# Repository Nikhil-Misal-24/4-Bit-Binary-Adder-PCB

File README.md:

# 4-Bit Binary Adder Using 74HC Logic ICs

A through-hole, discrete-logic **4-bit ripple-carry adder** built from 74HC86 (XOR), 74HC08 (AND) and 74HC32 (OR) ICs, with push-button inputs, LED indicators and a PCB designed in **KiCad**.

> **Project status:** The schematic and final PCB layout are complete in KiCad. This README makes **no claim** that the board has been fabricated, assembled or tested. All results below are *theoretical expected values*. Items marked **⚠ Confirm** should be checked before fabrication.

## At a Glance

| Parameter | Specification |
|---|---|
| Function | Adds two 4-bit unsigned binary numbers |
| Inputs | 8 push switches: A0–A3 and B0–B3 |
| Output | 5-bit result `Cout S3 S2 S1 S0` (range 0 to 30) on 5 LEDs |
| Architecture | Half adder (bit 0) + three full adders (bits 1–3), ripple-carry |
| Logic ICs | 2× 74HC86 (XOR), 2× 74HC08 (AND), 1× 74HC32 (OR) |
| Supply | Regulated 5 V DC via barrel jack, fuse and power switch |
| PCB | KiCad, through-hole, appears to be 2-layer |
| Hardware status | Fabrication and testing **not yet verified** |

---

## Table of Contents

1. [Introduction](#1-introduction)
2. [Project Overview](#2-project-overview)
3. [Key Features](#3-key-features)
4. [Objectives and Learning Outcomes](#4-objectives-and-learning-outcomes)
5. [Working Principle of a 4-Bit Binary Adder](#5-working-principle-of-a-4-bit-binary-adder)
6. [Boolean Expressions and Logic Equations](#6-boolean-expressions-and-logic-equations)
7. [Circuit Architecture and Block Diagram](#7-circuit-architecture-and-block-diagram)
8. [Hardware Components](#8-hardware-components)
9. [Input and Output Explanation](#9-input-and-output-explanation)
10. [Circuit Operation: Worked Example](#10-circuit-operation-worked-example)
11. [Expected Output and Verification Test Cases](#11-expected-output-and-verification-test-cases)
12. [Power Supply Requirements and Safety Precautions](#12-power-supply-requirements-and-safety-precautions)
13. [PCB Design Details and KiCad Files](#13-pcb-design-details-and-kicad-files)
14. [Repository Folder Structure](#14-repository-folder-structure)
15. [How to Open the Project in KiCad](#15-how-to-open-the-project-in-kicad)
16. [Testing and Troubleshooting](#16-testing-and-troubleshooting)
17. [Applications](#17-applications)
18. [Limitations and Possible Future Improvements](#18-limitations-and-possible-future-improvements)
19. [Skills Demonstrated](#19-skills-demonstrated)
20. [Author and Acknowledgements](#20-author-and-acknowledgements)

---

## 1. Introduction

Adders are the foundation of every arithmetic logic unit (ALU). This project implements a 4-bit binary adder **using only basic logic gates** (XOR, AND, OR) instead of a ready-made adder IC such as the 74HC283. Building it gate by gate makes the carry mechanism visible and testable on real hardware.

## 2. Project Overview

The circuit adds two 4-bit unsigned numbers, **A (A3 A2 A1 A0)** and **B (B3 B2 B1 B0)**, entered with eight push switches. The result is a **5-bit value** shown on five LEDs:

```
Result = Cout S3 S2 S1 S0
```

- **S0–S3** are the four sum bits (S0 = LSB).
- **Cout** is the final carry out of bit 3 and acts as the fifth (most significant) result bit.

The maximum result is 1111 + 1111 = 11110 (15 + 15 = 30), which needs 5 bits.

The board also has eight **input-indicator LEDs** (D1–D8) that mirror the state of each input switch, plus five **output LEDs** (D9–D13).

## 3. Key Features

- Pure gate-level design: 2× 74HC86, 2× 74HC08, 1× 74HC32.
- Two 4-bit inputs, 5-bit output (sum + carry).
- Input-state LEDs for each switch, so the entered operands can be read directly from the board.
- 10 kΩ pull-down resistors for defined logic-low inputs.
- Five 100 nF decoupling capacitors (C1–C5), one beside each IC.
- 220 Ω series resistors on every LED.
- Power entry through a barrel jack with a fuse and an on/off switch.
- Through-hole, breadboard-style parts, easy to hand-solder and probe.
- Silkscreen reference table for 4-bit values 0–15 on the board.
- Complete KiCad schematic and 2-layer PCB layout.

## 4. Objectives and Learning Outcomes

**Objectives**

- Design a multi-bit adder from XOR, AND and OR gates.
- Translate a schematic into a PCB layout using KiCad.
- Add clear user interface elements (switches, LEDs, silkscreen) to a logic board.

**Learning outcomes**

- Derive half-adder and full-adder equations and cascade them.
- Understand ripple-carry propagation and its speed limitation.
- Understand CMOS logic practice: pull-downs, unused-input handling, decoupling and LED current limiting.
- Practice schematic capture, footprint assignment, routing, DRC and design documentation.

## 5. Working Principle of a 4-Bit Binary Adder

Binary addition works like decimal addition, column by column, from the least significant bit (LSB) to the most significant bit (MSB). In each column we add two input bits plus the carry coming from the previous column.

| Building block | Inputs | Outputs | Used for |
|---|---|---|---|
| **Half adder** | A, B | Sum, Carry | Bit 0 (no carry-in) |
| **Full adder** | A, B, Cin | Sum, Cout | Bits 1, 2, 3 |

**Ripple-carry principle.** The carry-out of each stage feeds the carry-in of the next stage:

```
C0 = 0 → [Bit 0] → C1 → [Bit 1] → C2 → [Bit 2] → C3 → [Bit 3] → C4 = Cout
```

Bit *i* cannot produce a valid sum until the carry from bit *i−1* has settled. The carry therefore "ripples" from the LSB to the MSB. The worst case (e.g. `1111 + 0001`) makes the carry travel through all four stages, which is why the delay grows with word length.

## 6. Boolean Expressions and Logic Equations

For each bit *i*, define the **propagate** signal $P_i$ and **generate** signal $G_i$:

$$P_i = A_i \oplus B_i \qquad G_i = A_i \cdot B_i$$

**Bit 0 (half adder, $C_0 = 0$):**

$$S_0 = A_0 \oplus B_0 \qquad C_1 = A_0 \cdot B_0$$

**Bits 1 to 3 (full adder):**

$$S_i = A_i \oplus B_i \oplus C_i = P_i \oplus C_i$$

$$C_{i+1} = A_i B_i + (A_i \oplus B_i)\,C_i = G_i + P_i C_i$$

**Final carry (fifth output bit):**

$$C_{out} = C_4$$

**Gate budget (derived from the equations):**

| Gate type | Needed | Available (ICs fitted) | Spare |
|---|---|---|---|
| XOR (74HC86) | 7 | 8 (2 ICs) | 1 |
| AND (74HC08) | 7 | 8 (2 ICs) | 1 |
| OR (74HC32) | 3 | 4 (1 IC) | 1 |

Gate truth tables:

| A | B | XOR (A⊕B) | AND (A·B) | OR (A+B) |
|:-:|:-:|:-:|:-:|:-:|
| 0 | 0 | 0 | 0 | 0 |
| 0 | 1 | 1 | 0 | 1 |
| 1 | 0 | 1 | 0 | 1 |
| 1 | 1 | 0 | 1 | 1 |

## 7. Circuit Architecture and Block Diagram

### 7.1 System-level block diagram

The design is split into four functional blocks: **power**, **input stage**, **logic core** and **output stage**.

```mermaid
flowchart LR
    PWR["POWER<br/>J1 - F1 - SW1<br/>regulated +5 V"]

    subgraph INP["INPUT STAGE"]
        direction TB
        SWA["SW2, SW4, SW6, SW8<br/>Operand A (A0-A3)"]
        SWB["SW3, SW5, SW7, SW9<br/>Operand B (B0-B3)"]
        IND["10 kOhm pull-downs<br/>Indicator LEDs D1-D8"]
    end

    subgraph CORE["LOGIC CORE - 74HC ICs"]
        direction TB
        XORS["XOR: U1, U2<br/>74HC86"]
        ANDS["AND: U3, U4<br/>74HC08"]
        ORS["OR: U5<br/>74HC32"]
    end

    subgraph OUT["OUTPUT STAGE"]
        direction TB
        RES["220 Ohm resistors<br/>R17-R21"]
        LEDS["LEDs D13-D9<br/>Cout S3 S2 S1 S0"]
    end

    PWR -- "INPUT_VCC" --> INP
    PWR -- "VCC + C1-C5" --> CORE
    INP -- "A0-A3, B0-B3" --> CORE
    CORE -- "S0-S3, Cout" --> OUT
```

### 7.2 Functional blocks

| Block | Reference designators | Function | Key signals |
|---|---|---|---|
| **Power** | J1, F1, SW1, C1–C5 | Accepts regulated 5 V DC, protects with a fuse, switches the supply, decouples each IC | `INPUT_VCC`, `GND` |
| **Input stage** | SW2–SW9, R2/R3/R5/R7/R9/R11/R13/R15, D1–D8, R1/R4/R6/R8/R10/R12/R14/R16 | Converts switch positions into clean logic levels and shows each level on an LED | A0–A3, B0–B3 |
| **XOR section** | U1, U2 (74HC86) | Computes propagate signals $P_i$ and sum bits $S_i$ | $P_i$, $S_i$ |
| **AND section** | U3, U4 (74HC08) | Computes generate signals $G_i$ and carry-propagate terms $P_i C_i$ | $G_i$, $P_i C_i$ |
| **OR section** | U5 (74HC32) | Combines $G_i$ and $P_i C_i$ into the next carry | $C_{i+1}$ |
| **Output stage** | R17–R21, D9–D13 | Displays S0–S3 and Cout | `Cout S3 S2 S1 S0` |

### 7.3 Bit-slice architecture

The adder is built from four identical bit slices. Bit 0 has no carry-in, so it needs only a **half adder**. Bits 1 to 3 each use a **full adder** made from two XOR gates, two AND gates and one OR gate.

**Full-adder slice (bits 1–3):**

```mermaid
flowchart LR
    Ai["Ai"] --> X1["XOR 1"]
    Bi["Bi"] --> X1
    Ai --> A1["AND 1"]
    Bi --> A1

    X1 -- "Pi" --> X2["XOR 2"]
    Ci["Ci (carry-in)"] --> X2
    X1 -- "Pi" --> A2["AND 2"]
    Ci --> A2

    X2 --> Si["Si (sum)"]
    A1 -- "Gi" --> O1["OR"]
    A2 -- "Pi AND Ci" --> O1
    O1 --> Co["C(i+1) (carry-out)"]
```

**Half-adder slice (bit 0):**

```mermaid
flowchart LR
    A0["A0"] --> XH["XOR"]
    B0["B0"] --> XH
    A0 --> AH["AND"]
    B0 --> AH
    XH --> S0["S0 (sum)"]
    AH --> C1["C1 (carry-out)"]
```

### 7.4 Gate allocation per stage

| Stage | Type | XOR | AND | OR | Outputs |
|---|---|:-:|:-:|:-:|---|
| Bit 0 | Half adder | 1 | 1 | 0 | S0, C1 |
| Bit 1 | Full adder | 2 | 2 | 1 | S1, C2 |
| Bit 2 | Full adder | 2 | 2 | 1 | S2, C3 |
| Bit 3 | Full adder | 2 | 2 | 1 | S3, C4 = Cout |
| **Required** | | **7** | **7** | **3** | |
| **Available** (2× 74HC86, 2× 74HC08, 1× 74HC32) | | 8 | 8 | 4 | |
| **Spare** | | 1 | 1 | 1 | Unused inputs must be tied to a defined level |

The exact gate-to-pin assignment is defined in the KiCad schematic and is not repeated here.

### 7.5 Ripple-carry chain

The carry-out of each slice drives the carry-in of the next one. The fifth result bit, Cout, is the carry-out of bit 3.

```mermaid
flowchart LR
    IN0["A0, B0"] --> HA0["Bit 0<br/>Half adder"]
    IN1["A1, B1"] --> FA1["Bit 1<br/>Full adder"]
    IN2["A2, B2"] --> FA2["Bit 2<br/>Full adder"]
    IN3["A3, B3"] --> FA3["Bit 3<br/>Full adder"]

    HA0 -- "C1" --> FA1
    FA1 -- "C2" --> FA2
    FA2 -- "C3" --> FA3

    HA0 --> S0["S0"]
    FA1 --> S1["S1"]
    FA2 --> S2["S2"]
    FA3 --> S3["S3"]
    FA3 -- "C4" --> COUT["Cout"]
```

### 7.6 Signal timing (derived from topology)

Counting the number of gates a signal passes through gives the **logic depth**. Assuming all inputs change at the same instant:

| Signal | Path | Depth (gate delays) |
|---|---|:-:|
| S0, C1 | XOR or AND of A0, B0 | 1 |
| S1 | XOR(P1, C1) | 2 |
| C2 | AND(P1, C1) → OR with G1 | 3 |
| S2 | XOR(P2, C2) | 4 |
| C3 | AND(P2, C2) → OR with G2 | 5 |
| S3 | XOR(P3, C3) | 6 |
| **Cout (C4)** | AND(P3, C3) → OR with G3 | **7** |

Each ripple stage adds two gate delays (one AND plus one OR) to the carry path, so the worst case is `1111 + 0001`. These depths come from the circuit structure, **not from measurement**; actual propagation delay depends on the 74HC datasheet values, supply voltage and load.

### 7.7 Input and output channel structure

Each of the eight inputs and five outputs uses the same circuit pattern.

```mermaid
flowchart LR
    subgraph IC["Input channel (x8)"]
        direction LR
        VCC1["INPUT_VCC"] --> SW["Push switch"]
        SW --> NODE(("Logic node"))
        NODE --> PD["10 kOhm to GND"]
        NODE --> RL["220 Ohm"] --> LD["LED to GND"]
        NODE --> GI["Gate input"]
    end

    subgraph OC["Output channel (x5)"]
        direction LR
        GO["Gate output"] --> RO["220 Ohm"] --> LO["LED to GND"]
    end
```

| Channel | Idle state | Active state | Notes |
|---|---|---|---|
| Input | Pulled to GND by 10 kΩ (logic 0), LED off | Switch connects node to `INPUT_VCC` (logic 1), LED on | Switch type (latching or momentary) to be confirmed |
| Output | Gate output low, LED off | Gate output high, LED on (active-high) | LED current set by the 220 Ω series resistor |

### 7.8 Power distribution

```mermaid
flowchart LR
    ADP["Regulated 5 V adapter"] --> J1["J1<br/>barrel jack"]
    J1 --> F1["F1<br/>fuse"]
    F1 --> SW1["SW1<br/>power switch"]
    SW1 --> RAIL["INPUT_VCC rail"]

    RAIL --> ICS["U1-U5<br/>pin 14 (VCC)"]
    RAIL --> SWS["Input switches<br/>SW2-SW9"]
    CAPS["C1-C5<br/>100 nF"] -. "decoupling" .-> ICS
    GND["GND plane/net"] --- ICS
    GND --- CAPS
```

The same `INPUT_VCC` rail powers the ICs and provides the logic-high level for the input switches. There is no on-board regulator, so the adapter must supply a regulated 5 V (see [Section 12](#12-power-supply-requirements-and-safety-precautions)).

### 7.9 Physical placement versus logical function

| PCB area | Contents | Logical role |
|---|---|---|
| Top row, left to right | U1 (XOR-1), U3 (AND-1), U5 (OR), U4 (AND-2), U2 (XOR-2), with C1–C5 between them | Logic core |
| Middle left (two rows of four) | SW2, SW4, SW6, SW8 / SW3, SW5, SW7, SW9 | Operand entry |
| Middle right (framed array) | D1–D8 | Input-state indicators |
| Bottom of LED frame | D13 D12 D11 D10 D9 | Output: Cout S3 S2 S1 S0 (left to right) |
| Bottom left | J1, F1, SW1 | Power entry |
| Bottom centre | 10 kΩ bank (R2, R3, R5, R7, R9, R11, R13, R15) and 220 Ω bank (R1, R4, R6, R8, R10, R12, R14, R16–R21) | Pull-downs and LED current limiting |

## 8. Hardware Components

Quantities are taken from the KiCad schematic and PCB silkscreen.

| Ref. | Component | Qty | Purpose |
|---|---|:-:|---|
| U (×2) | 74HC86, quad 2-input XOR, DIP-14 | 2 | Sum bits and propagate signals |
| U (×2) | 74HC08, quad 2-input AND, DIP-14 | 2 | Generate and propagate-carry terms |
| U (×1) | 74HC32, quad 2-input OR, DIP-14 | 1 | Combines carry terms |
| SW2–SW9 | DPDT push switch (`SW_Push_DPDT` symbol) | 8 | Enter A3–A0 and B3–B0 |
| D1–D8 | LED | 8 | Show the state of each input |
| D9–D13 | LED | 5 | Display S0–S3 and Cout |
| R2, R3, R5, R7, R9, R11, R13, R15 | 10 kΩ resistor | 8 | Input pull-downs |
| R1, R4, R6, R8, R10, R12, R14, R16 | 220 Ω resistor | 8 | Current limit for input LEDs |
| R17–R21 | 220 Ω resistor | 5 | Current limit for output LEDs |
| J1 | DC barrel jack | 1 | 5 V supply input |
| F1 | Small fuse | 1 | Overcurrent protection (**⚠ Confirm rating**) |
| SW1 | Slide power switch | 1 | Supply on/off |
| H1, H2 | Mounting holes | 2 | Mechanical mounting (**⚠ Confirm size**) |
| C1–C5 | 100 nF ceramic decoupling capacitor | 5 | Local supply decoupling, one beside each IC |
| *C (optional)* | 10–100 µF electrolytic bulk capacitor | 1 | **Not in the current design.** Recommended near J1 (hand-fit or add in a future revision) |

Optional: DIP-14 IC sockets (recommended for easy IC replacement).

Total: 5 ICs, 8 switches, 13 LEDs, 8× 10 kΩ resistors, 13× 220 Ω resistors and 5× 100 nF capacitors.

## 9. Input and Output Explanation

### Inputs

| Operand bit | Switch | Schematic net | Weight |
|---|---|---|:-:|
| A0 | SW2 | A1 | 2⁰ |
| B0 | SW3 | B1 | 2⁰ |
| A1 | SW4 | A2 | 2¹ |
| B1 | SW5 | B2 | 2¹ |
| A2 | SW6 | A3 | 2² |
| B2 | SW7 | B3 | 2² |
| A3 | SW8 | A4 | 2³ |
| B3 | SW9 | B4 | 2³ |

> **⚠ Confirm:** The schematic names the bit pairs A1/B1 … A4/B4, while this README uses A0–A3 and B0–B3 (standard LSB = bit 0 notation). The mapping above assumes "Input-1" is the least significant pair. Verify against the netlist.

Each switch connects its signal node to `INPUT_VCC` (logic 1) when actuated; a 10 kΩ pull-down holds the node at GND (logic 0) otherwise. An LED with a 220 Ω resistor on the same node shows the current logic level. **⚠ Confirm** whether the chosen switch is latching or momentary, since this determines how operands are held.

### Outputs

| LED | Meaning | Schematic net (assumed) |
|---|---|---|
| D13 | **Cout** (MSB, bit 4) | `OR_Y4` |
| D12 | S3 | `4OUT` |
| D11 | S2 | `3OUT` |
| D10 | S1 | `2OUT` |
| D9 | S0 (LSB) | `1OUT` |

Read the output LEDs left to right on the PCB as **D13 D12 D11 D10 D9 = Cout S3 S2 S1 S0**.

> **⚠ Confirm:** The schematic annotations label `1OUT` as "Bit-1 (MSB)" and `OR_Y4` as "Bit-5 (LSB)". By the adder equations, `1OUT` should be the LSB sum and the final OR output should be Cout (MSB), so those annotations look reversed. Correct the schematic text or the net assignments so documentation and hardware agree.

## 10. Circuit Operation: Worked Example

**Example:** `1111 + 0001` (15 + 1 = 16)

A = 1111 (A3 A2 A1 A0), B = 0001 (B3 B2 B1 B0)

| Stage | Ai | Bi | Cin | Pi = Ai⊕Bi | Si = Pi⊕Cin | Gi = Ai·Bi | Pi·Cin | Cout(i) = Gi + Pi·Cin |
|:-:|:-:|:-:|:-:|:-:|:-:|:-:|:-:|:-:|
| Bit 0 | 1 | 1 | 0 (none) | 0 | **0** | 1 | 0 | **1** |
| Bit 1 | 1 | 0 | 1 | 1 | **0** | 0 | 1 | **1** |
| Bit 2 | 1 | 0 | 1 | 1 | **0** | 0 | 1 | **1** |
| Bit 3 | 1 | 0 | 1 | 1 | **0** | 0 | 1 | **1** |

Final carry out = 1, so:

```
    1 1 1 1     (A = 15)
  + 0 0 0 1     (B =  1)
  ---------
  1 0 0 0 0     → Cout S3 S2 S1 S0 = 1 0 0 0 0 = 16
```

Expected LED state: **D13 ON**, D12, D11, D10, D9 OFF. The carry created at bit 0 ripples through bits 1, 2 and 3 before appearing as Cout.

## 11. Expected Output and Verification Test Cases

> All values below are **theoretical**. The "Result on hardware" column is intentionally blank until real testing is done.

| # | Category | A (A3..A0) | B (B3..B0) | Expected Cout S3 S2 S1 S0 | Decimal | Result on hardware |
|:-:|---|:-:|:-:|:-:|:-:|:-:|
| 1 | Zero inputs | 0000 | 0000 | 0 0000 | 0 | ☐ |
| 2 | Zero + value | 0101 | 0000 | 0 0101 | 5 | ☐ |
| 3 | Single bit | 0001 | 0001 | 0 0010 | 2 | ☐ |
| 4 | Basic addition | 0010 | 0011 | 0 0101 | 5 | ☐ |
| 5 | Basic addition | 0101 | 0011 | 0 1000 | 8 | ☐ |
| 6 | Basic addition | 1010 | 0101 | 0 1111 | 15 (no carry-out) | ☐ |
| 7 | Short carry chain | 0011 | 0001 | 0 0100 | 4 | ☐ |
| 8 | Longer carry chain | 0111 | 0001 | 0 1000 | 8 | ☐ |
| 9 | Full carry chain | 1111 | 0001 | 1 0000 | 16 | ☐ |
| 10 | Carry-out | 0110 | 1010 | 1 0000 | 16 | ☐ |
| 11 | Carry-out | 1001 | 0111 | 1 0000 | 16 | ☐ |
| 12 | Carry-out | 1000 | 1000 | 1 0000 | 16 | ☐ |
| 13 | Maximum inputs | 1111 | 1111 | 1 1110 | 30 | ☐ |

Recommended practice: test all 256 input combinations if possible (for example with a script that prints expected values to compare against the board), and record results in `tests/test_log.md`.

## 12. Power Supply Requirements and Safety Precautions

### Supply

- The design requires a **regulated 5 V DC supply**. The 74HC family is specified for a limited supply range (typically about 2 V to 6 V; **verify against the datasheet of the exact parts**), and it is **not** safe to feed unregulated or higher voltages.
- The schematic power block is labelled for **5 V DC**. The board has only a barrel jack, fuse and switch and **no voltage regulator**, so use a regulated 5 V adapter. Never connect a 12 V (or any unregulated) adapter to J1.
- **⚠ Confirm** the barrel-jack polarity and plug size of your adapter against the J1 footprint (centre-positive is typical).

### Estimated current (calculation, not a measurement)

Assuming a red LED forward voltage of about 2 V (**⚠ Confirm** with your LED datasheet):

$$I_{LED} \approx \frac{5\,\text{V} - 2\,\text{V}}{220\,\Omega} \approx 13.6\ \text{mA}$$

Worst case with all 13 LEDs lit is about 177 mA, plus a small amount through the pull-down resistors and the ICs' quiescent current. Choose the fuse and supply accordingly (**⚠ Confirm fuse rating**).

### Pre-fabrication checks (important)

1. **Decoupling capacitors.** C1–C5 (100 nF) are placed beside the ICs in the final layout. **Verify** on the PCB that each sits close to its IC's VCC (pin 14) and GND (pin 7), and consider adding a 10–100 µF bulk capacitor near J1.
2. **LED current and gate drive.** A 220 Ω resistor gives roughly 13 mA, which may exceed the DC output current that 74HC gates are specified to drive at guaranteed logic levels (a few mA at 5 V; check the datasheet). Output LEDs are driven directly by gate outputs, so **verify** the resistor values, and consider larger values (for example 470 Ω to 1 kΩ) or a buffer if brightness is acceptable.
3. **Unused gate inputs.** One XOR, one AND and one OR gate are spare. Unused CMOS inputs must be tied to GND or VCC, never left floating. **Verify** this in the schematic (a floating input can cause extra current draw and noise).

### Safety precautions

- Power off (SW1) before inserting or removing ICs.
- Observe LED and IC orientation (pin 1 marker).
- Take ESD precautions when handling CMOS ICs.
- Check for solder bridges and verify no short between VCC and GND with a multimeter before first power-up.

## 13. PCB Design Details and KiCad Files

### 13.1 Design summary (from the KiCad screenshots)

| Item | Detail |
|---|---|
| EDA tool | KiCad (**⚠ Confirm version**) |
| Technology | Through-hole components, DIP-14 ICs |
| Layers | Appears to be 2-layer (red front copper, blue back copper in the PCB editor) |
| Ground | Copper fill/zone visible on the back side (**⚠ Confirm** zone settings) |
| Silkscreen | IC names (XOR-1, AND-1, OR, AND-2, XOR-2), switch and LED references, "10k Pull Down" and "220ohm for LEDs" resistor groups, BCD 0–15 reference table, KiCad logo |
| Layout | ICs along the top, switches in two rows, LED array on the right, resistor banks and power entry along the bottom |
| Decoupling | C1–C5 (100 nF) placed between/beside the ICs |
| Mounting | Mounting holes H1 and H2 visible (**⚠ Confirm** count/size) |

### 13.2 Items intentionally not specified

The following are **not documented because they have not been provided**; add them once confirmed: board dimensions, board thickness, copper weight, trace width and clearance rules, minimum drill, surface finish, fabricator and fabrication date.

### 13.3 Project images

| Image | Suggested file |
|---|---|
| Schematic overview | `images/schematic.png` |
| PCB editor (copper layout) | `images/pcb_layout.png` |
| 3D view, bare board | `images/3d_board_only.png` |
| 3D view, with components | `images/3d_board_assembled.png` |
| 3D view, back side | `images/3d_back.png` |

```markdown

```

### 13.4 Items to confirm before fabrication

Resolved in the final revision: reference designators now match between schematic and PCB (U1–U5), and decoupling capacitors C1–C5 were added.

| # | Observation | Action |
|:-:|---|---|
| 1 | Schematic labels `1OUT` as "Bit-1 (MSB)" and the last output as "Bit-5 (LSB)"; by the adder equations this looks reversed (see Section 9) | Correct the annotations and verify net assignment |
| 2 | No bulk capacitor near the power entry | Optional: add 10–100 µF near J1 |
| 3 | 5 V input with no regulator or reverse-polarity protection | Use a regulated 5 V adapter; consider adding protection |
| 4 | 220 Ω on gate-driven output LEDs (about 13 mA estimated) | Verify against 74HC output current ratings; consider larger values |
| 5 | Spare gates (one XOR, one AND, one OR) | Confirm unused inputs are tied to GND or VCC |
| 6 | Silkscreen table titled "BCD" lists 0–15; sums go up to 30 | Consider renaming to "Binary / Decimal" |
| 7 | Switch type (latching vs momentary) | Confirm and document |
| 8 | ERC and DRC reports | Run both and add to `hardware/reports/` |
| 9 | Board dimensions, mounting-hole size, KiCad version | Add once confirmed |

## 14. Repository Folder Structure

*Suggested layout; adjust to match your actual files.*

```text
4-bit-binary-adder-74hc/
├── README.md
├── LICENSE
├── .gitignore
├── hardware/
│   ├── kicad/
│   │   ├── 4bit_adder.kicad_pro
│   │   ├── 4bit_adder.kicad_sch
│   │   ├── 4bit_adder.kicad_pcb
│   │   └── fp-info-cache            (optional, may be git-ignored)
│   ├── libraries/
│   │   ├── symbols/                 (custom .kicad_sym, if any)
│   │   ├── footprints/              (custom .pretty folders, if any)
│   │   └── 3dmodels/                (.step / .wrl, if any)
│   └── reports/
│       ├── erc_report.txt
│       └── drc_report.txt
├── manufacturing/                   (add only after files are generated and checked)
│   ├── gerbers/
│   ├── drill/
│   ├── bom/
│   │   └── bom.csv
│   └── placement/
│       └── pos.csv
├── docs/
│   ├── schematic.pdf
│   ├── datasheets/                  (74HC86, 74HC08, 74HC32)
│   └── theory.md                    (optional extended theory)
├── images/
│   ├── schematic.png
│   ├── pcb_layout.png
│   ├── 3d_board_only.png
│   ├── 3d_board_assembled.png
│   └── 3d_back.png
└── tests/
    └── test_log.md                  (record real measurements here)
```

## 15. How to Open the Project in KiCad

1. Install KiCad (use a version equal to or newer than the one used to create the project, **⚠ Confirm version**).
2. Clone the repository:
   ```bash
   git clone https://github.com/<your-username>/4-bit-binary-adder-74hc.git
   cd 4-bit-binary-adder-74hc/hardware/kicad
   ```
3. Open `4bit_adder.kicad_pro` in KiCad.
4. Double-click the **Schematic Editor** to view the circuit, or the **PCB Editor** to view the layout.
5. Make sure custom libraries in `hardware/libraries/` are registered (*Preferences → Manage Symbol/Footprint Libraries → Project Specific Libraries*).
6. Run **Inspect → Electrical Rules Checker** (schematic) and **Inspect → Design Rules Checker** (PCB).
7. Use **View → 3D Viewer** (Alt+3) to inspect the board.
8. Generate Gerbers via **File → Fabrication Outputs** only after resolving the items in [Section 13.4](#134-items-to-confirm-before-fabrication).

## 16. Testing and Troubleshooting

### Suggested test procedure (not yet performed)

1. **Visual inspection:** component orientation, solder joints, no bridges.
2. **Continuity check:** confirm no short between 5 V and GND before power-up.
3. **Power-on:** apply regulated 5 V, check each IC has about 5 V between its VCC and GND pins.
4. **Input check:** actuate each switch and verify the matching input LED (D1–D8) responds.
5. **Functional test:** step through the table in [Section 11](#11-expected-output-and-verification-test-cases) and record results.

### Troubleshooting

| Symptom | Possible cause | What to check |
|---|---|---|
| No LEDs light at all | No power, blown fuse, SW1 off | Supply voltage, F1 continuity, SW1 position |
| IC gets hot | Reversed supply, short or wrong IC orientation | Power off immediately; check polarity and pin 1 |
| Input LED does not respond | Switch wiring/type, LED reversed, missing resistor | Switch continuity, LED polarity |
| Sum bit wrong, others correct | Faulty gate, bad solder joint or wrong IC pin | Probe the XOR/AND outputs for that stage |
| Carry never appears (Cout stays off) | Carry path broken between stages | Probe C1, C2, C3 with a multimeter or logic probe |
| Random or flickering outputs | Floating input, missing decoupling | Tie unused inputs; add 100 nF capacitors |
| LEDs dim or inconsistent logic levels | Gate overloaded by LED current | Increase LED resistor value |

## 17. Applications

- Teaching digital logic and computer arithmetic in labs.
- Demonstrating ripple-carry operation and carry propagation visually.
- Building block for a simple ALU (add the subtract and logic-function stages).
- Foundation for studying faster adders (carry-lookahead, carry-select).
- A hands-on example of the PCB design workflow from schematic to layout.

## 18. Limitations and Possible Future Improvements

**Limitations**

- Unsigned 4-bit operands only (no signed overflow indication).
- Ripple-carry delay grows with each added bit; propagation delay has not been measured.
- Eight manual switches make entering test patterns slow.
- No on-board regulator or reverse-polarity protection.
- Hardware has not been fabricated or verified (as of this documentation).

**Possible improvements**

- Add a bulk capacitor and a 5 V regulator stage with reverse-polarity protection.
- Replace switches with DIP switches or a microcontroller test header for automatic testing.
- Add a carry-in input (turns the half adder at bit 0 into a full adder) and a subtract mode using XOR-controlled inversion of B.
- Add a carry-lookahead version and compare delays.
- Add a seven-segment or decimal display for the 0–30 result.
- Simulate the design (e.g. in KiCad's ngspice or a logic simulator) and add the results.
- Add test points, ERC/DRC reports and a full BOM with manufacturer part numbers.

## 19. Skills Demonstrated

- Combinational logic design and Boolean algebra
- Half-adder / full-adder derivation and ripple-carry analysis
- 74HC-series IC selection and CMOS design practice
- Schematic capture and PCB layout in KiCad
- Hardware design review (power, LED current, unused inputs, decoupling)
- Technical documentation and GitHub project organisation
- Test planning and troubleshooting methodology

## 20. Author and Acknowledgements

**Author:** `<Your Name>`
Electronics and Communication Engineering, `<Your College / University>`
GitHub: `<link>` | LinkedIn: `<link>` | Email: `<email>`

**Acknowledgements**

- KiCad EDA project and community.
- Manufacturer datasheets for the 74HC86, 74HC08 and 74HC32.
- `<Faculty guide / mentors / online resources you used>`

**License:** `<Choose one, e.g. MIT for documentation/software and CERN-OHL-P for hardware>`

---

*This documentation describes the design as captured in the KiCad files. Items marked ⚠ Confirm are unverified and should be resolved before ordering the PCB.*

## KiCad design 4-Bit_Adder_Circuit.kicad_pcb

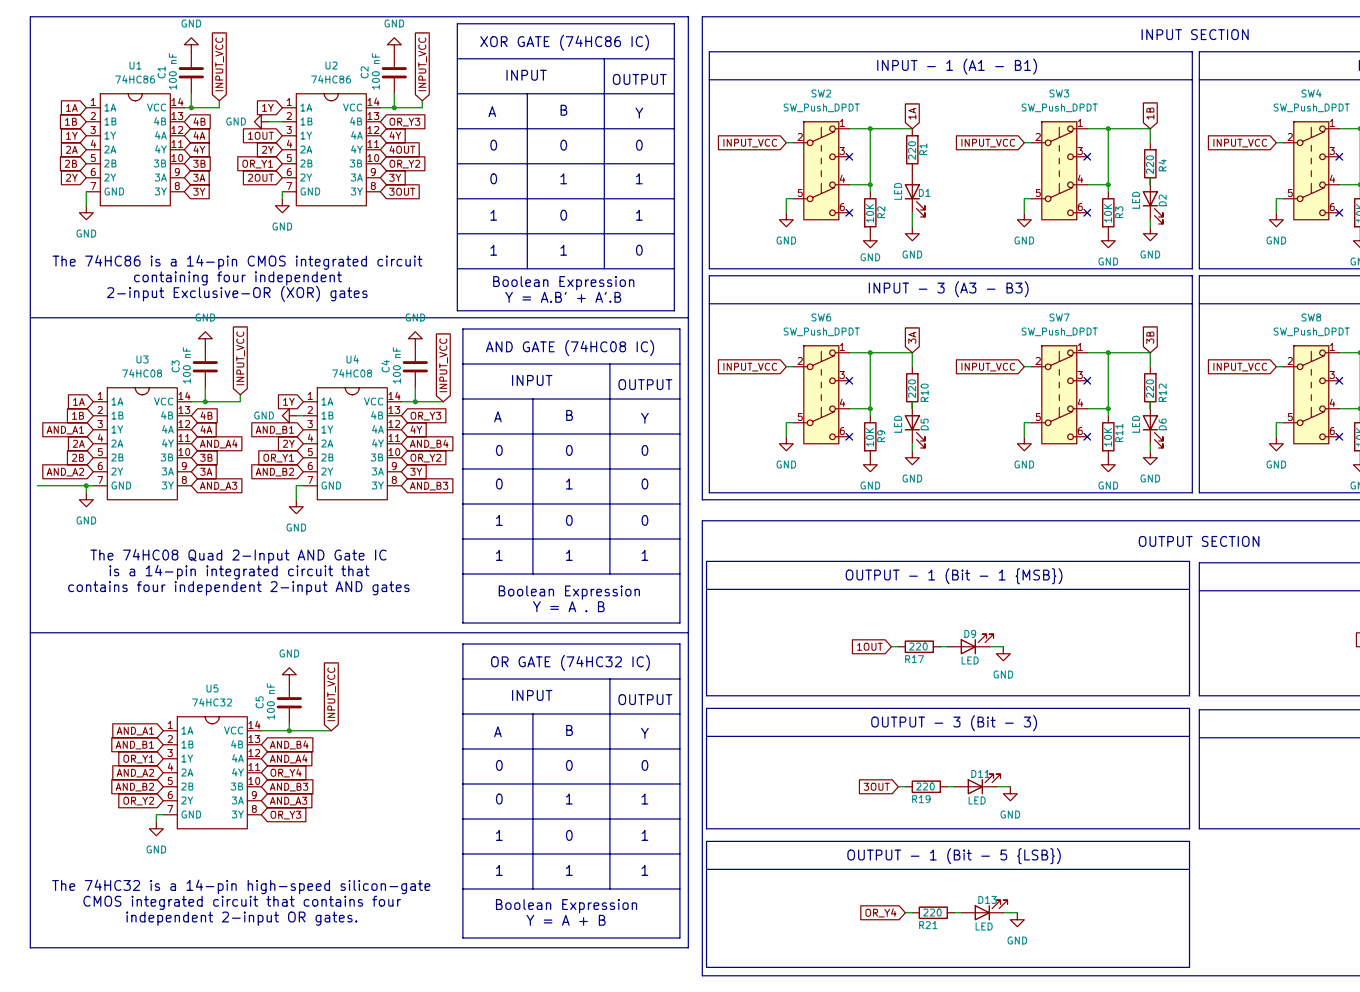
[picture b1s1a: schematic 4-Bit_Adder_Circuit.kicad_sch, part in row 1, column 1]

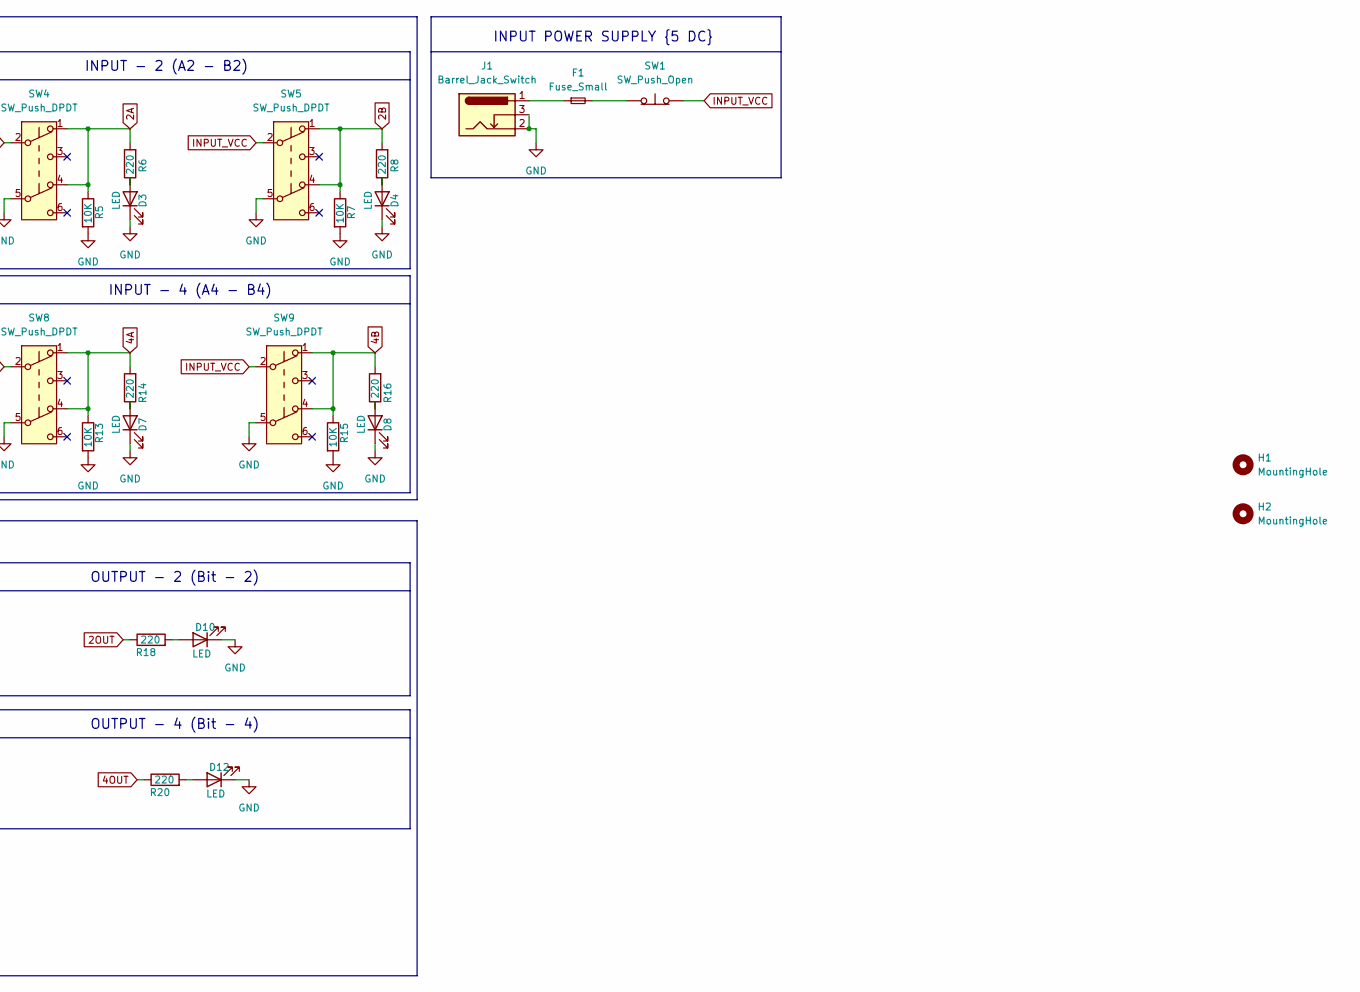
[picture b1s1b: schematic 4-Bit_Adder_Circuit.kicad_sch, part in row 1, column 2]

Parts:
C1, C2, C3, C4, C5: 100 nF; C_Disc_D3.0mm_W1.6mm_P2.50mm
D1, D2, D3, D4, D5, D6, D7, D8, D9, D10, D11, D12, D13: LED; LED_D4.0mm
F1: Fuse_Small; Fuse_Littelfuse_395Series
H1, H2: MountingHole; MountingHole_2.7mm_Pad_Via
J1: Barrel_Jack_Switch; BarrelJack_Kycon_KLDX-0202-xC_Horizontal
R1, R4, R6, R8, R10, R12, R14, R16, R17, R18, R19, R20, R21: 220; R_Axial_DIN0207_L6.3mm_D2.5mm_P10.16mm_Horizontal
R2, R3, R5, R7, R9, R11, R13, R15: 10K; R_Axial_DIN0207_L6.3mm_D2.5mm_P10.16mm_Horizontal
SW1: SW_Push_Open; SW_DIP_SPSTx01_Slide_6.7x4.1mm_W7.62mm_P2.54mm_LowProfile
SW2: SW_Push_DPDT; SW_Push_2P2T_Toggle_CK_PVA2OAH5xxxxxxV2
SW3, SW4, SW5, SW6, SW7, SW8, SW9: SW_Push_DPDT; SW_Push_2P2T_Toggle_CK_PVA2xxH3xxxxxxV2
U1, U2: 74HC86; DIP-14_W10.16mm
U3, U4: 74HC08; DIP-14_W10.16mm
U5: 74HC32; DIP-14_W10.16mm

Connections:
1A: R1.2, R2.1, SW2.1 (A), SW2.4 (A), U1.1 (1A), U3.1 (1A)
1B: R3.1, R4.2, SW3.1 (A), SW3.4 (A), U1.2 (1B), U3.2 (1B)
1OUT: R17.1, U2.3 (1Y)
1Y: U1.3 (1Y), U2.1 (1A), U4.1 (1A)
2A: R5.1, R6.2, SW4.1 (A), SW4.4 (A), U1.4 (2A), U3.4 (2A)
2B: R7.1, R8.2, SW5.1 (A), SW5.4 (A), U1.5 (2B), U3.5 (2B)
2OUT: R18.1, U2.6 (2Y)
2Y: U1.6 (2Y), U2.4 (2A), U4.4 (2A)
3A: R9.1, R10.2, SW6.1 (A), SW6.4 (A), U1.9 (3A), U3.9 (3A)
3B: R11.1, R12.2, SW7.1 (A), SW7.4 (A), U1.10 (3B), U3.10 (3B)
3OUT: R19.1, U2.8 (3Y)
3Y: U1.8 (3Y), U2.9 (3A), U4.9 (3A)
4A: R13.1, R14.2, SW8.1 (A), SW8.4 (A), U1.12 (4A), U3.12 (4A)
4B: R15.1, R16.2, SW9.1 (A), SW9.4 (A), U1.13 (4B), U3.13 (4B)
4OUT: R20.1, U2.11 (4Y)
4Y: U1.11 (4Y), U2.12 (4A), U4.12 (4A)
AND_A1: U3.3 (1Y), U5.1 (1A)
AND_A2: U3.6 (2Y), U5.4 (2A)
AND_A3: U3.8 (3Y), U5.9 (3A)
AND_A4: U3.11 (4Y), U5.12 (4A)
AND_B1: U4.3 (1Y), U5.2 (1B)
AND_B2: U4.6 (2Y), U5.5 (2B)
AND_B3: U4.8 (3Y), U5.10 (3B)
AND_B4: U4.11 (4Y), U5.13 (4B)
GND: C1.2, C2.2, C3.2, C4.2, C5.2, D1.1 (K), D2.1 (K), D3.1 (K), D4.1 (K), D5.1 (K), D6.1 (K), D7.1 (K), D8.1 (K), D9.1 (K), D10.1 (K), D11.1 (K), D12.1 (K), D13.1 (K), J1.2, J1.3, R2.2, R3.2, R5.2, R7.2, R9.2, R11.2, R13.2, R15.2, SW2.5 (B), SW3.5 (B), SW4.5 (B), SW5.5 (B), SW6.5 (B), SW7.5 (B), SW8.5 (B), SW9.5 (B), U1.7 (GND), U2.2 (1B), U2.7 (GND), U3.7 (GND), U4.2 (1B), U4.7 (GND), U5.7 (GND)
INPUT_VCC: C1.1, C2.1, C3.1, C4.1, C5.1, SW1.2 (B), SW2.2 (B), SW3.2 (B), SW4.2 (B), SW5.2 (B), SW6.2 (B), SW7.2 (B), SW8.2 (B), SW9.2 (B), U1.14 (VCC), U2.14 (VCC), U3.14 (VCC), U4.14 (VCC), U5.14 (VCC)
unnamed: D1.2 (A), R1.1
unnamed: D2.2 (A), R4.1
unnamed: D3.2 (A), R6.1
unnamed: D4.2 (A), R8.1
unnamed: D5.2 (A), R10.1
unnamed: D6.2 (A), R12.1
unnamed: D7.2 (A), R14.1
unnamed: D8.2 (A), R16.1
unnamed: D9.2 (A), R17.2
unnamed: D10.2 (A), R18.2
unnamed: D11.2 (A), R19.2
unnamed: D12.2 (A), R20.2
unnamed: D13.2 (A), R21.2
unnamed: F1.1, J1.1
unnamed: F1.2, SW1.1 (A)
OR_Y1: U2.5 (2B), U4.5 (2B), U5.3 (1Y)
OR_Y2: U2.10 (3B), U4.10 (3B), U5.6 (2Y)
OR_Y3: U2.13 (4B), U4.13 (4B), U5.8 (3Y)
OR_Y4: R21.1, U5.11 (4Y)

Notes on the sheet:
OUTPUT - 2 (Bit - 2)
OUTPUT - 1 (Bit - 1 {MSB})
INPUT SECTION
OUTPUT - 1 (Bit - 5 {LSB})
OUTPUT
OUTPUT - 3 (Bit - 3)
INPUT
INPUT - 4 (A4 - B4)
INPUT - 2 (A2 - B2)
Boolean Expression Y = A + B
The 74HC08 Quad 2-Input AND Gate IC is a 14-pin integrated circuit that contains four independent 2-input AND gates
The 74HC86 is a 14-pin CMOS integrated circuit containing four independent 2-input Exclusive-OR (XOR) gates
OUTPUT - 4 (Bit - 4)
OR GATE (74HC32 IC)
OUTPUT SECTION
Boolean Expression Y = A.B' + A'.B
The 74HC32 is a 14-pin high-speed silicon-gate CMOS integrated circuit that contains four independent 2-input OR gates.
XOR GATE (74HC86 IC)
INPUT - 1 (A1 - B1)
INPUT POWER SUPPLY {5 DC}
AND GATE (74HC08 IC)
Boolean Expression Y = A . B
INPUT - 3 (A3 - B3)

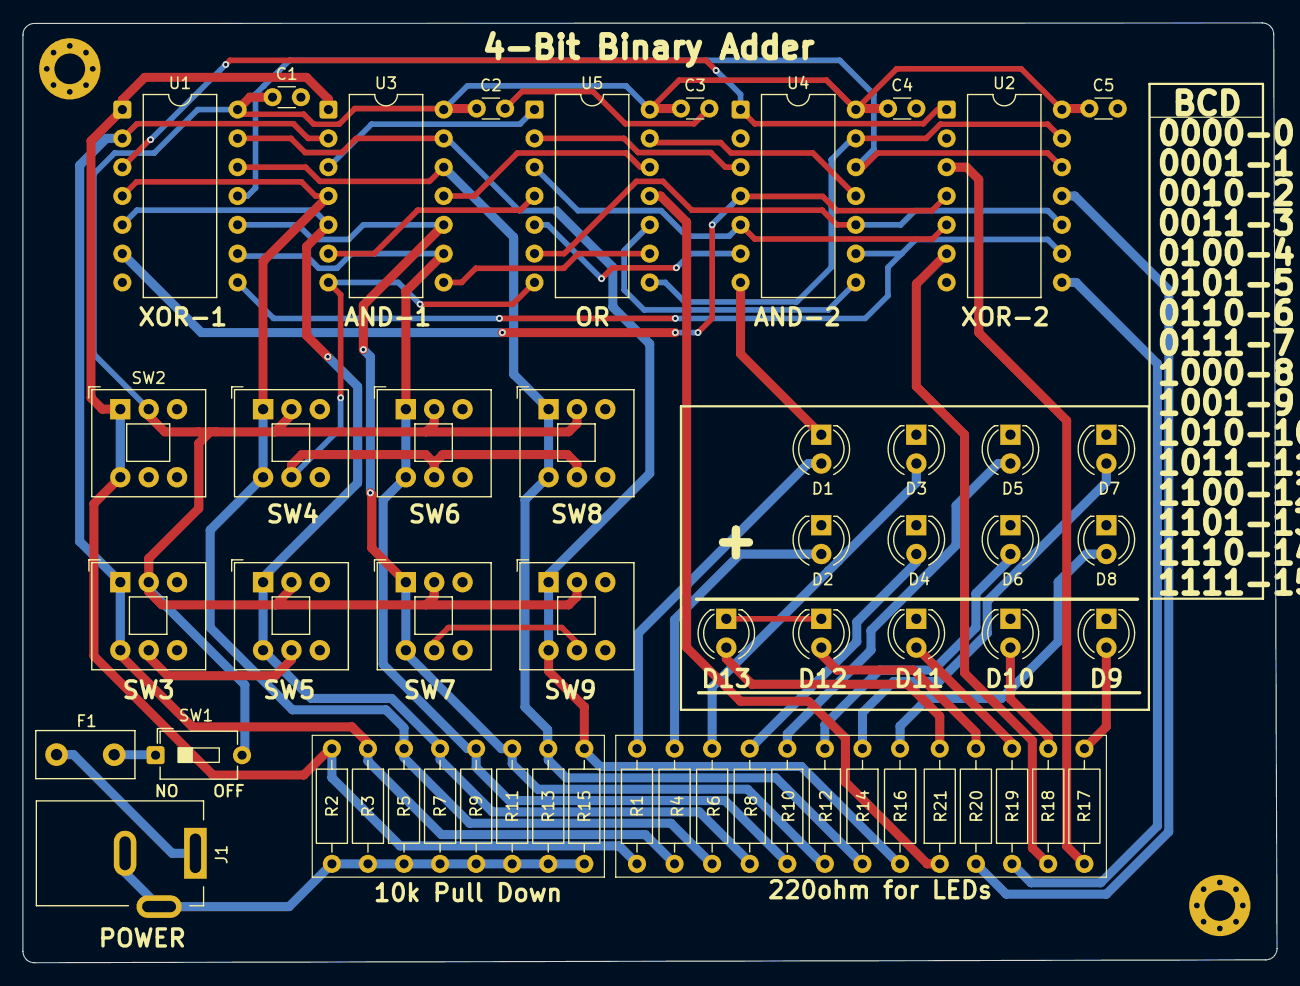
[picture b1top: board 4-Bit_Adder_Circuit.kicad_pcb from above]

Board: 2 copper layers, 110.5 x 82.8 mm, 57 parts (0 on the bottom side), 45 nets.
